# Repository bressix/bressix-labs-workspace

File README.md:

# bressix-labs-workspace

> Engineering Research & Development Laboratory
>
> Laboratório de Pesquisa e Desenvolvimento em Engenharia

---

*As versões em PT-BR estão disponíveis nos blocos expansíveis de cada seção.*

## Proof of Concept / Em Desenvolvimento

This repository is the main engineering workspace for **bressix LABs**.

Here you'll find projects at different stages of development. Some are production-ready and actively maintained, while others are early prototypes, experiments, or ongoing research. That diversity is intentional and reflects how we approach engineering.

We believe good engineering evolves through iteration. Ideas are tested, designs are refined, and documentation grows alongside the project. Rather than waiting for everything to be perfect, we prefer to share our work as it evolves.

Not every repository follows the same structure, contains the same level of documentation, or has the same degree of maturity. Each project is documented according to its own complexity and current stage of development.

The purpose of this workspace is to build, document, and share engineering projects as they evolve.

<details>
<summary><strong>PT-BR</strong></summary>

Este repositório é o principal ambiente de engenharia da **bressix LABs**.

Aqui você encontrará projetos em diferentes estágios de desenvolvimento. Alguns estão prontos para uso e são mantidos ativamente, enquanto outros ainda são protótipos, experimentos ou pesquisas em andamento. Essa diversidade é intencional e reflete a forma como fazemos engenharia.

Acreditamos que boa engenharia evolui por meio da iteração. Ideias são testadas, projetos são refinados e a documentação cresce junto com o próprio desenvolvimento. Em vez de esperar que tudo esteja perfeito, preferimos compartilhar nosso trabalho à medida que ele evolui.

Nem todos os repositórios seguem a mesma estrutura, possuem o mesmo nível de documentação ou apresentam o mesmo grau de maturidade. Cada projeto é documentado de acordo com sua complexidade e seu estágio de desenvolvimento.

O propósito deste workspace é construir, documentar e compartilhar projetos de engenharia à medida que evoluem.

</details>

## Disclaimer

#### NO WARRANTY

THIS WORKSPACE, INCLUDING ALL SOFTWARE, FIRMWARE, HARDWARE DESIGNS, SCHEMATICS, AND OTHER ASSETS, IS PROVIDED **"AS IS"**, WITHOUT WARRANTY OF ANY KIND, EXPRESS OR IMPLIED, INCLUDING, BUT NOT LIMITED TO, WARRANTIES OF MERCHANTABILITY, FITNESS FOR A PARTICULAR PURPOSE, NON-INFRINGEMENT, SECURITY, FUNCTIONALITY, RELIABILITY, OR HARDWARE SAFETY.

THE AUTHORS, CONTRIBUTORS, AND COPYRIGHT HOLDERS SHALL NOT BE LIABLE FOR ANY CLAIM, DAMAGES, LOSS OF DATA, DEVICE BRICKING, HARDWARE FAILURE, SECURITY INCIDENT, SERVICE INTERRUPTION, OR OTHER LIABILITY, WHETHER IN AN ACTION OF CONTRACT, TORT, OR OTHERWISE, ARISING FROM, OUT OF, OR IN CONNECTION WITH THIS WORKSPACE OR THE USE OF ANY SOFTWARE, FIRMWARE, HARDWARE DESIGN, SCHEMATIC, OR OTHER ASSET PROVIDED HEREIN.

USING, COMPILING, FLASHING, MODIFYING, OR DEPLOYING ANY CODE, FIRMWARE, HARDWARE DESIGN, OR OTHER ASSET FROM THIS REPOSITORY IS ENTIRELY AT YOUR OWN RISK.

THIS DISCLAIMER APPLIES TO THE ENTIRE WORKSPACE UNLESS A SPECIFIC PROJECT EXPLICITLY STATES OTHERWISE.

<details>
<summary><strong>PT-BR</strong></summary>

#### SEM GARANTIAS

ESTE WORKSPACE, INCLUINDO TODOS OS SOFTWARES, FIRMWARES, PROJETOS DE HARDWARE, ESQUEMÁTICOS E DEMAIS ATIVOS, É FORNECIDO **"NO ESTADO EM QUE SE ENCONTRA"**, SEM GARANTIAS DE QUALQUER NATUREZA, EXPRESSAS OU IMPLÍCITAS, INCLUINDO, MAS NÃO SE LIMITANDO A, GARANTIAS DE COMERCIALIZAÇÃO, ADEQUAÇÃO A UMA FINALIDADE ESPECÍFICA, NÃO VIOLAÇÃO, SEGURANÇA, FUNCIONALIDADE, CONFIABILIDADE OU INTEGRIDADE FÍSICA DO HARDWARE.

OS AUTORES, COLABORADORES E DETENTORES DOS DIREITOS AUTORAIS NÃO PODERÃO SER RESPONSABILIZADOS POR QUAISQUER RECLAMAÇÕES, DANOS, PERDA DE DADOS, INUTILIZAÇÃO DE DISPOSITIVOS (DEVICE BRICKING), FALHAS DE HARDWARE, INCIDENTES DE SEGURANÇA, INTERRUPÇÕES DE SERVIÇO OU OUTRAS RESPONSABILIDADES DECORRENTES DO USO DESTE WORKSPACE OU DE QUALQUER SOFTWARE, FIRMWARE, PROJETO DE HARDWARE, ESQUEMÁTICO OU OUTRO ATIVO DISPONIBILIZADO NESTE REPOSITÓRIO.

O USO, A COMPILAÇÃO, A GRAVAÇÃO (FLASHING), A MODIFICAÇÃO OU A IMPLANTAÇÃO DE QUALQUER CÓDIGO, FIRMWARE, PROJETO DE HARDWARE OU OUTRO ATIVO DESTE REPOSITÓRIO É DE INTEIRA RESPONSABILIDADE DO USUÁRIO.

ESTA ISENÇÃO DE RESPONSABILIDADE APLICA-SE A TODO O WORKSPACE, EXCETO QUANDO UM PROJETO ESPECÍFICO DECLARAR EXPRESSAMENTE O CONTRÁRIO.

</details>

## Security Notice

No private keys, cryptographic seeds, production certificates, active service tokens, customer credentials, or confidential corporate information are stored or tracked within this repository.

Development workflows follow repository sanitization practices, strict `.gitignore` policies, and isolated local environments to prevent accidental disclosure of sensitive information.

Local engineering activities should rely on detached configuration files, environment variables, or `.env` templates that are never committed to version control.

Repositories may intentionally include placeholder files, sample certificates, mock credentials, or template configurations for demonstration purposes. Such artifacts are non-functional and intended solely for development, testing, or documentation.

<details>
<summary><strong>PT-BR</strong></summary>

Nenhuma chave privada, semente criptográfica, certificado de produção, token ativo de serviço, credencial de cliente ou informação corporativa confidencial é armazenada ou rastreada neste repositório.

Os fluxos de desenvolvimento seguem práticas de higienização do repositório, políticas rigorosas de `.gitignore` e ambientes locais isolados para reduzir o risco de exposição acidental de informações sensíveis.

As atividades locais de engenharia devem utilizar arquivos de configuração desacoplados, variáveis de ambiente ou templates `.env` que nunca sejam enviados ao controle de versão.

Os repositórios podem conter arquivos de exemplo, certificados fictícios, credenciais simuladas ou configurações modelo destinados exclusivamente à demonstração, desenvolvimento, testes ou documentação. Esses artefatos não são funcionais e não representam credenciais reais.

</details>

## Mission Statement

bressix LABs exists to advance engineering through practical research, experimentation, and open documentation.

Our work spans multiple disciplines—including hardware, embedded systems, Linux, information security, PKI, automation, infrastructure, and applied research—but the mission remains the same: building practical solutions, documenting technical decisions, and sharing knowledge that others can study, reproduce, and extend.

We believe engineering knowledge becomes more valuable when it is documented, reproducible, and shared.

<details>
<summary><strong>PT-BR</strong></summary>

A bressix LABs existe para promover a engenharia por meio de pesquisa prática, experimentação e documentação aberta.

Nosso trabalho abrange diversas áreas — incluindo hardware, sistemas embarcados, Linux, segurança da informação, PKI, automação, infraestrutura e pesquisa aplicada — mas a missão permanece a mesma: desenvolver soluções práticas, documentar decisões técnicas e compartilhar conhecimento para que outras pessoas possam estudá-lo, reproduzi-lo e expandi-lo.

Acreditamos que o conhecimento de engenharia se torna mais valioso quando é documentado, reproduzível e compartilhado.

</details>

## Engineering Values

The projects in this workspace are diverse, but they are usually guided by the same engineering values.

- Simplicity is preferred over unnecessary complexity.
- Technical decisions are documented, not just their outcomes.
- Projects are shared as they evolve.
- Engineering history is preserved whenever it provides context or future value.
- Structure exists to support engineering, never the other way around.
- Practical solutions come before elegant abstractions.

These values are descriptive rather than prescriptive. They reflect the experience accumulated across different projects, not a checklist applied to every repository.

<details>
<summary><strong>PT-BR</strong></summary>

Os projetos deste workspace são bastante diferentes entre si, mas normalmente são guiados pelos mesmos valores de engenharia.

- Preferimos simplicidade à complexidade desnecessária.
- Documentamos decisões técnicas, não apenas seus resultados.
- Compartilhamos projetos à medida que evoluem.
- Preservamos o histórico de engenharia sempre que ele agrega contexto ou valor futuro.
- A estrutura existe para servir à engenharia, nunca o contrário.
- Soluções práticas vêm antes de abstrações elegantes.

Esses valores são descritivos, não prescritivos. Eles refletem a experiência acumulada em diferentes projetos, e não um checklist aplicado a todos os repositórios.

</details>

## Engineering Philosophy

We believe engineering is an iterative process.

Projects rarely begin as complete platforms. Most start as small experiments, evolve through practical use, and mature one decision at a time.

We strive to keep repositories as simple as possible, documentation proportional to each project's complexity, and engineering decisions easy to understand.

Nothing in this workspace exists simply because "every project should have one." Every component, document, script, and directory should exist because it serves a practical purpose.

<details>
<summary><strong>PT-BR</strong></summary>

Acreditamos que engenharia é um processo iterativo.

Projetos raramente nascem como plataformas completas. A maioria começa como pequenos experimentos, evolui por meio do uso prático e amadurece uma decisão de cada vez.

Buscamos manter os repositórios tão simples quanto possível, a documentação proporcional à complexidade de cada projeto e as decisões de engenharia fáceis de compreender.

Nada neste workspace existe apenas porque "todo projeto deveria ter". Cada componente, documento, script e diretório deve existir porque possui um propósito prático.

</details>

## Workspace Architecture

The workspace is organized by engineering domain rather than by technology or programming language. Each directory groups projects with similar objectives, allowing both the projects and the workspace to evolve naturally as new ideas, technologies, and research emerge.

```text
bressix-labs-workspace/
├── 3D/                        # Functional 3D modeling and mechanical CAD assets.
├── audio/                     # Audio engineering, DSP experiments, and acoustic studies.
├── firmware/                  # Embedded firmware development (ESP32, CH552, AVR, RP2350).
├── hardware/                  # Schematics, PCB layouts, hardware analysis, and pin mapping.
├── system-hacking-n-tuning/   # Linux customization, system tuning, drivers, and platform optimization.
├── tls-n-automation-scripts/  # PKI tooling, infrastructure utilities, automation scripts, and API integrations.
│   ├── cnpj_query/            # Resilient multi-provider CNPJ acquisition engine.
│   ├── globalsign-atlas-api/  # Atlas API integration modules.
│   ├── globalsign-gcc-api/    # Legacy GCC API integration modules.
│   ├── ssl-tls-auditing/      # TLS auditing and compliance validation tools.
│   ├── tls-crt/               # X.509 certificate manipulation utilities.
│   ├── tls-discovery/         # TLS asset discovery and inventory automation.
│   └── tls-scripts/           # Core cryptographic and infrastructure helper scripts.
└── WIP/                       # Experimental and unclassified development sandbox.
```

The structure is intentionally simple and may evolve as projects mature or new engineering domains are introduced.

<details>
<summary><strong>PT-BR</strong></summary>

O workspace é organizado por domínio de engenharia, e não por tecnologia ou linguagem de programação. Cada diretório reúne projetos com objetivos semelhantes, permitindo que tanto os projetos quanto o próprio workspace evoluam naturalmente à medida que novas ideias, tecnologias e pesquisas surgem.

A estrutura é intencionalmente simples e pode evoluir conforme os projetos amadurecem ou novos domínios de engenharia sejam incorporados.

</details>

## License

This workspace is licensed under the **GNU General Public License v3.0 (GPL-3.0)**.

Unless explicitly stated otherwise within an individual project, all source code, documentation, hardware designs, schematics, and other assets are distributed under the terms of the GPL-3.0.

See the [`LICENSE`](LICENSE) file for the complete license text.

<details>
<summary><strong>PT-BR</strong></summary>

Este workspace está licenciado sob a **GNU General Public License v3.0 (GPL-3.0)**.

Salvo indicação explícita em contrário dentro de um projeto específico, todo o código-fonte, documentação, projetos de hardware, esquemáticos e demais ativos são distribuídos sob os termos da GPL-3.0.

Consulte o arquivo [`LICENSE`](LICENSE) para o texto completo da licença.

</details>

---

Copyright (C) 2026 **bressix LABs**

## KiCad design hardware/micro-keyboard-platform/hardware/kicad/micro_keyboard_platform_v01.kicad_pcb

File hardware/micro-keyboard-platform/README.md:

# Micro Keyboard Platform (MKP)

> Modular physical keyboard platform for embedded systems.

---

## Overview

The **Micro Keyboard Platform (MKP)** is a compact and modular physical
keyboard platform designed for embedded systems.

MKP is not simply a keyboard matrix.

It is an active input device with its own microcontroller, responsible for
scanning the keyboard, processing key events, implementing layers and
communicating with the host system.

The central design principle is:

> **The MKP is a keyboard, not a keyboard matrix.**

The host does not need to know how the keyboard matrix works. It only needs
to consume the events generated by the MKP.

The current hardware revision is based on the **RP2040-Zero** and provides:

- 50 physical keys;
- 5 × 10 keyboard matrix;
- per-key diodes;
- native USB HID capability;
- UART host interface;
- I2C host interface;
- SPI host interface;
- programmable WS2812B RGB status indicator;
- dedicated external 5 V power input.

<details>
<summary><strong>PT-BR</strong></summary>

A **Micro Keyboard Platform (MKP)** é uma plataforma compacta e modular de
teclado físico desenvolvida para sistemas embarcados.

O MKP não é simplesmente uma matriz de teclas.

Ele é um dispositivo de entrada ativo, com seu próprio microcontrolador,
responsável pela varredura do teclado, processamento dos eventos,
implementação de layers e comunicação com o sistema hospedeiro.

O princípio central do projeto é:

> **O MKP é um teclado, não uma matriz de teclas.**

O host não precisa conhecer o funcionamento interno da matriz. Ele apenas
consome os eventos produzidos pelo MKP.

A revisão atual utiliza o **RP2040-Zero** e oferece:

- 50 teclas físicas;
- matriz 5 × 10;
- diodo individual por tecla;
- USB HID nativo;
- interface UART;
- interface I2C;
- interface SPI;
- indicador RGB programável WS2812B;
- entrada dedicada de alimentação externa de 5 V.

</details>

---

## Why MKP?

MKP originally started as a compact keyboard for a specific embedded
terminal.

During development, the project evolved beyond that original requirement.

Instead of creating a keyboard tied to one device, the architecture was
redesigned as an independent platform capable of being reused by different
hosts.

This allows the same keyboard hardware to be integrated into:

- microcontroller projects;
- Linux SBCs;
- portable terminals;
- cyberdecks;
- communication devices;
- instrumentation;
- experimental embedded systems;
- conventional computers through USB HID.

The hardware provides capabilities.

The firmware defines behavior.

<details>
<summary><strong>PT-BR</strong></summary>

O MKP nasceu originalmente como um teclado compacto para um terminal
embarcado específico.

Durante o desenvolvimento, o projeto evoluiu além dessa necessidade inicial.

Em vez de criar um teclado dependente de um único equipamento, a arquitetura
foi transformada em uma plataforma independente capaz de ser reutilizada por
diferentes hosts.

Isso permite utilizar o mesmo hardware em:

- projetos com microcontroladores;
- SBCs Linux;
- terminais portáteis;
- cyberdecks;
- equipamentos de comunicação;
- instrumentação;
- sistemas embarcados experimentais;
- computadores convencionais através de USB HID.

O hardware oferece capacidades.

O firmware define o comportamento.

</details>

---

## Architecture

~~~text
                         USB-C
                           │
                    ┌──────▼──────┐
                    │ RP2040-Zero │
                    │             │
                    │ Scan        │
                    │ Debounce    │
                    │ Keymap      │
                    │ Layers      │
                    │ Protocol    │
                    └──────┬──────┘
                           │
             ┌─────────────┼─────────────┐
             │             │             │
             ▼             ▼             ▼
        Matrix 5×10     Host I/O      WS2812B
          50 keys      UART/I2C/SPI     GP29
             │
             ▼
        Key events
~~~

The keyboard matrix belongs entirely to the MKP.

Matrix GPIOs are never exposed to the host.

---

## Keyboard

The Revision B keyboard uses a **5 × 10 electrical matrix** with
**50 physical switches**.

~~~text
┌────┬────┬────┬────┬────┬────┬────┬────┬────┬────┐
│ 1  │ 2  │ 3  │ 4  │ 5  │ 6  │ 7  │ 8  │ 9  │ 0  │
├────┼────┼────┼────┼────┼────┼────┼────┼────┼────┤
│ Q  │ W  │ E  │ R  │ T  │ Y  │ U  │ I  │ O  │ P  │
├────┼────┼────┼────┼────┼────┼────┼────┼────┼────┤
│ A  │ S  │ D  │ F  │ G  │ H  │ J  │ K  │ L  │ENT │
├────┼────┼────┼────┼────┼────┼────┼────┼────┼────┤
│ FN │CAPS│ Z  │ X  │ C  │ V  │ B  │ N  │ M  │CTRL│
└────┴────┴────┴────┴────┴────┴────┴────┴────┴────┘
~~~

The remaining switches provide:

~~~text
A / B / X / Y

UP / DOWN / LEFT / RIGHT

SPACE

SW49 — firmware-defined function
~~~

The exact function of special keys remains configurable by firmware.

---

## Hardware

| Component | Revision B |
|---|---|
| Controller | RP2040-Zero |
| Keyboard matrix | 5 × 10 |
| Physical switches | 50 |
| Switch type | 4.5 × 4.5 × 5.0 mm tactile |
| Matrix diodes | 1N4148W |
| Diode package | SOD-123 |
| RGB indicator | WS2812B-5050 |
| USB | Native RP2040 USB |
| Host connector | 4 signals + GND |
| Host protocols | UART / I2C / SPI |
| External power | 5 V |
| PCB | 2-layer FR-4 |
| PCB thickness | 1.6 mm |

---

## Host Interfaces

The MKP can communicate with a host through two fundamentally different
interfaces.

### USB

The native USB interface of the RP2040 allows the MKP to operate directly
as a USB HID keyboard.

### Embedded Host Interface

A dedicated connector exposes four configurable signals:

~~~text
HOST_SIG1
HOST_SIG2
HOST_SIG3
HOST_SIG4
GND
~~~

These signals support:

~~~text
UART
I2C
SPI
~~~

Protocol selection is handled entirely by firmware.

Revision B does **not** use hardware protocol-selection jumpers, ADC
identification or resistor networks.

---

## RGB Status Indicator

Revision B includes one **WS2812B-5050** addressable RGB LED connected to
GP29.

Its behavior is firmware-defined and may represent:

- initialization;
- active layer;
- communication mode;
- Caps Lock;
- activity;
- error conditions;
- application-specific status.

---

## Mechanical Philosophy

MKP follows a **mechanical-first** design approach.

Keyboard geometry is primarily determined by:

- ergonomics;
- key spacing;
- physical dimensions;
- enclosure constraints;
- future faceplate integration.

Electrical routing adapts to the keyboard geometry rather than defining it.

Revision B places:

~~~text
TOP
├── switches
└── WS2812B

BOTTOM
├── RP2040-Zero
├── matrix diodes
├── passive components
├── host connector
└── power connector
~~~

The earlier experimental dual-side footprints were intentionally removed
from Revision B.

---

## Repository Structure

~~~text
micro-keyboard-platform/
├── docs/
│   ├── mkp_electrical_specification.txt
│   ├── mkp_electrical_specification_legacy_2026-07-13.txt
│   ├── mkp_manifesto.txt
│   ├── mkp_manifesto_legacy_2026-07-13.txt
│   └── inspiracao.jpeg
│
├── firmware/
│   └── src/
│
├── hardware/
│   ├── datasheets/
│   ├── kicad/
│   │   ├── footprints/
│   │   ├── micro_keyboard_platform_v01.kicad_pcb
│   │   ├── micro_keyboard_platform_v01.kicad_pro
│   │   ├── micro_keyboard_platform_v01.kicad_sch
│   │   └── micro_keyboard_platform_v01.net
│   │
│   └── production/
│       ├── bom/
│       └── gerbers/
│
├── mechanical/
│   ├── enclosure/
│   └── faceplate/
│
├── .gitignore
└── README.md
~~~

---

## Documentation

The project documentation is intentionally separated by purpose.

### Current documentation

- [Project Manifesto](docs/mkp_manifesto.txt)  
  Design philosophy, project identity and architectural principles.

- [Electrical Specification](docs/mkp_electrical_specification.txt)  
  Electrical architecture, GPIO mapping, interfaces, matrix behavior and
  Revision B implementation details.

### Historical documentation

Previous project documents are preserved instead of being overwritten:

- [Legacy Manifesto — 2026-07-13](docs/mkp_manifesto_legacy_2026-07-13.txt)
- [Legacy Electrical Specification — 2026-07-13](docs/mkp_electrical_specification_legacy_2026-07-13.txt)

Engineering history is intentionally preserved when it helps explain how
the project evolved.

---

## Revision B Status

**Current stage: prototype development**

### Completed

- [x] Platform architecture
- [x] 5 × 10 matrix
- [x] 50-key layout
- [x] RP2040-Zero controller
- [x] GPIO mapping
- [x] Electrical schematic
- [x] Host interface
- [x] External power input
- [x] WS2812B status indicator
- [x] TOP/BOTTOM component organization
- [x] Preliminary component placement
- [x] Main component selection
- [x] Electrical architecture freeze

### In progress

- [ ] Receive production components
- [ ] Physically validate footprints
- [ ] Freeze final placement
- [ ] Route PCB
- [ ] Run final DRC
- [ ] Generate Gerbers
- [ ] Manufacture prototype
- [ ] Assemble prototype
- [ ] Electrical bring-up
- [ ] Keyboard matrix validation
- [ ] USB HID validation
- [ ] UART validation
- [ ] I2C validation
- [ ] SPI validation
- [ ] Firmware implementation

---

## Development Flow

~~~text
Components
    │
    ▼
Footprint validation
    │
    ▼
Final placement
    │
    ▼
PCB routing
    │
    ▼
DRC
    │
    ▼
Gerbers
    │
    ▼
Prototype
    │
    ▼
Bring-up
    │
    ▼
Firmware
    │
    ▼
Validation
~~~

MKP is developed incrementally.

Design decisions that depend on physical tolerances or real components are
validated against actual hardware before being considered final.

---

## Design Principles

The Revision B architecture reflects a few core engineering principles:

- The MKP is a keyboard, not a keyboard matrix.
- The host consumes events instead of controlling the matrix.
- Hardware provides capabilities; firmware defines behavior.
- Mechanical requirements come before routing convenience.
- Useful flexibility should be preserved.
- Complexity without practical benefit should be removed.
- Engineering decisions and their history should be documented.
- The platform must remain independent from any single host.

---

## License

This project is part of **bressix LABs** and follows the license of the
parent workspace unless explicitly stated otherwise.

**GNU General Public License v3.0 — GPL-3.0**

See the workspace `LICENSE` file for the complete license text.

---

## bressix LABs

**Micro Keyboard Platform** is developed as part of **bressix LABs**.

> Engineering Research & Development Laboratory  
> Laboratório de Pesquisa e Desenvolvimento em Engenharia

The workspace covers hardware, embedded systems, Linux, information
security, PKI, automation, infrastructure and applied engineering research.

---

Copyright (C) 2026 **bressix LABs**

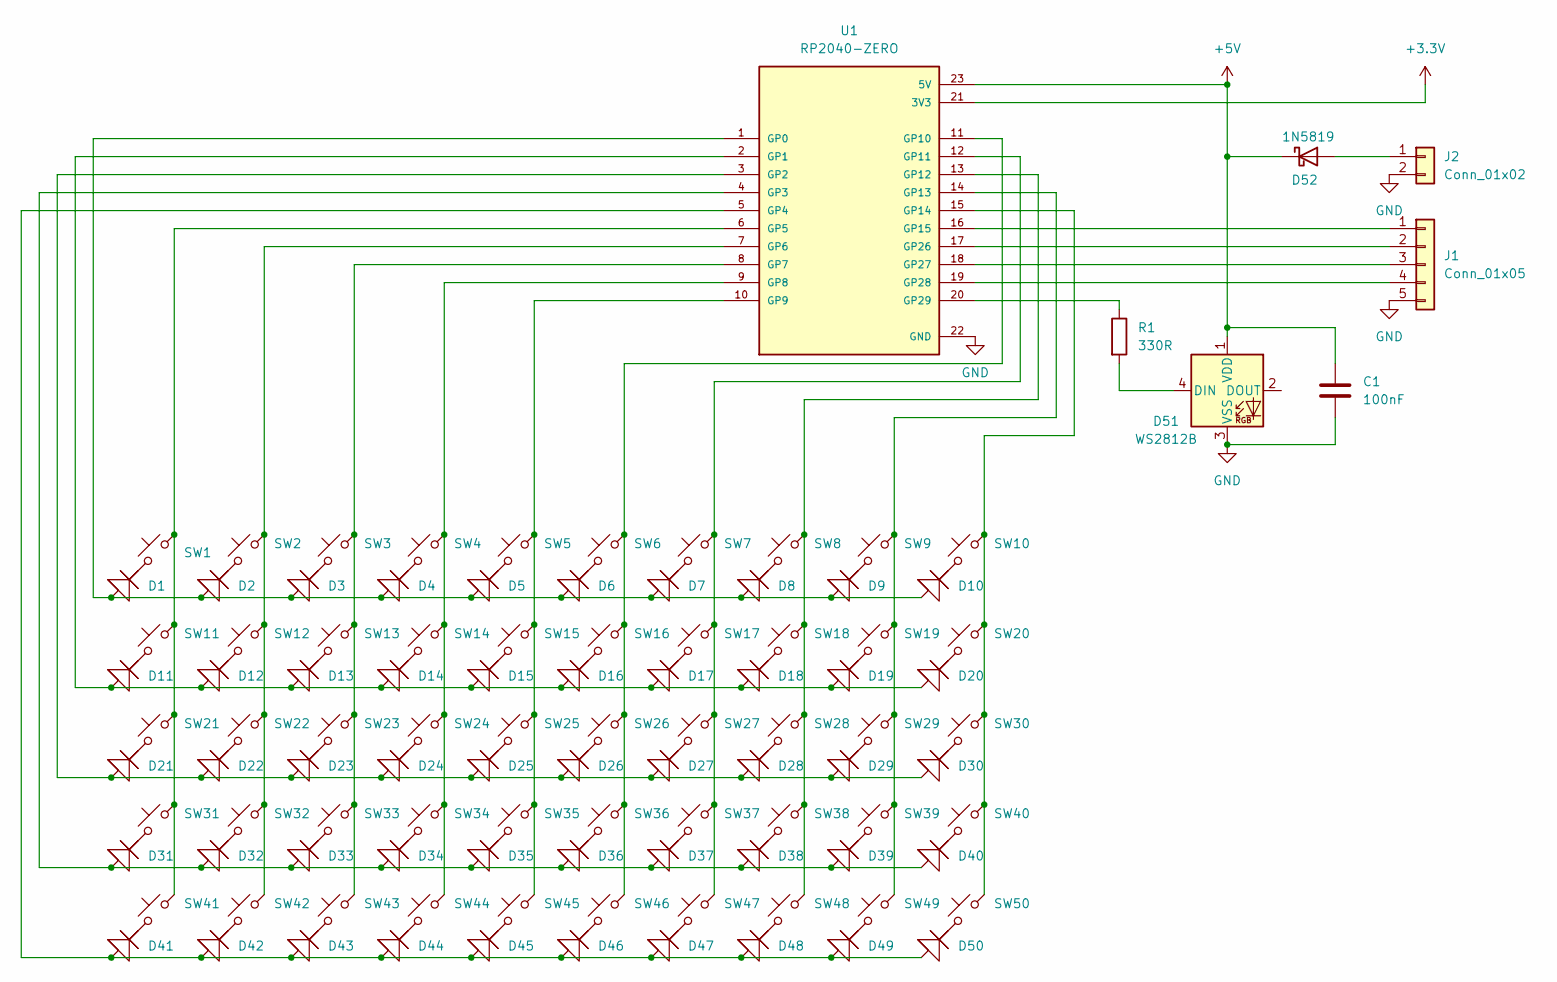
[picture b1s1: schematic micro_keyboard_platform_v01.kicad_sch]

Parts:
C1: 100nF; Capacitor_SMD_C_1206_3216Metric_BOTTON
D1, D2, D3, D4, D5, D6, D7, D8, D9, D10, D11, D12, D13, D14, D15, D16, D17, D18, D19, D20, D21, D22, D23, D24, D25, D26, D27, D28, D29, D30, D31, D32, D33, D34, D35, D36, D37, D38, D39, D40, D41, D42, D43, D44, D45, D46, D47, D48, D49, D50: 1N4148; D_SOD-123
D51: WS2812B; LED_WS2812B_PLCC4_5.0x5.0mm_P3.2mm
D52: 1N5819; Resistor_SMD_R_2010_5025Metric_BOTTON
J1: Conn_01x05; conn_01x05_hybrid_BOTTON
J2: Conn_01x02; JST_PH_S2B-PH-K_1x02_P2.00mm_Horizontal_BOTTON
R1: 330R; Resistor_SMD_R_2010_5025Metric_BOTTON
SW1, SW2, SW3, SW4, SW5, SW6, SW7, SW8, SW9, SW10, SW11, SW12, SW13, SW14, SW15, SW16, SW17, SW18, SW19, SW20, SW21, SW22, SW23, SW24, SW25, SW26, SW27, SW28, SW29, SW30, SW31, SW32, SW33, SW34, SW35, SW36, SW37, SW38, SW39, SW40, SW41, SW42, SW43, SW44, SW45, SW46, SW47, SW48, SW49, SW50: SW_Push_45deg; sw_push_4.5x4.5mm
U1: RP2040-ZERO; RP2040_ZERO_casteled_BOTTON; PARTREV NA

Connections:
+3.3V: U1.21 (3V3)
+5V: C1.1, D51.1 (VDD), D52.1 (K), U1.23 (5V)
GND: C1.2, D51.3 (VSS), J1.5, J2.2, U1.22 (GND)
unnamed: D1.1 (Anode), D2.1 (Anode), D3.1 (Anode), D4.1 (Anode), D5.1 (Anode), D6.1 (Anode), D7.1 (Anode), D8.1 (Anode), D9.1 (Anode), D10.1 (Anode), U1.1 (GP0)
unnamed: D1.2 (Cathode), SW1.1
unnamed: D2.2 (Cathode), SW2.1
unnamed: D3.2 (Cathode), SW3.1
unnamed: D4.2 (Cathode), SW4.1
unnamed: D5.2 (Cathode), SW5.1
unnamed: D6.2 (Cathode), SW6.1
unnamed: D7.2 (Cathode), SW7.1
unnamed: D8.2 (Cathode), SW8.1
unnamed: D9.2 (Cathode), SW9.1
unnamed: D10.2 (Cathode), SW10.1
unnamed: D11.1 (Anode), D12.1 (Anode), D13.1 (Anode), D14.1 (Anode), D15.1 (Anode), D16.1 (Anode), D17.1 (Anode), D18.1 (Anode), D19.1 (Anode), D20.1 (Anode), U1.2 (GP1)
unnamed: D11.2 (Cathode), SW11.1
unnamed: D12.2 (Cathode), SW12.1
unnamed: D13.2 (Cathode), SW13.1
unnamed: D14.2 (Cathode), SW14.1
unnamed: D15.2 (Cathode), SW15.1
unnamed: D16.2 (Cathode), SW16.1
unnamed: D17.2 (Cathode), SW17.1
unnamed: D18.2 (Cathode), SW18.1
unnamed: D19.2 (Cathode), SW19.1
unnamed: D20.2 (Cathode), SW20.1
unnamed: D21.1 (Anode), D22.1 (Anode), D23.1 (Anode), D24.1 (Anode), D25.1 (Anode), D26.1 (Anode), D27.1 (Anode), D28.1 (Anode), D29.1 (Anode), D30.1 (Anode), U1.3 (GP2)
unnamed: D21.2 (Cathode), SW21.1
unnamed: D22.2 (Cathode), SW22.1
unnamed: D23.2 (Cathode), SW23.1
unnamed: D24.2 (Cathode), SW24.1
unnamed: D25.2 (Cathode), SW25.1
unnamed: D26.2 (Cathode), SW26.1
unnamed: D27.2 (Cathode), SW27.1
unnamed: D28.2 (Cathode), SW28.1
unnamed: D29.2 (Cathode), SW29.1
unnamed: D30.2 (Cathode), SW30.1
unnamed: D31.1 (Anode), D32.1 (Anode), D33.1 (Anode), D34.1 (Anode), D35.1 (Anode), D36.1 (Anode), D37.1 (Anode), D38.1 (Anode), D39.1 (Anode), D40.1 (Anode), U1.4 (GP3)
unnamed: D31.2 (Cathode), SW31.1
unnamed: D32.2 (Cathode), SW32.1
unnamed: D33.2 (Cathode), SW33.1
unnamed: D34.2 (Cathode), SW34.1
unnamed: D35.2 (Cathode), SW35.1
unnamed: D36.2 (Cathode), SW36.1
unnamed: D37.2 (Cathode), SW37.1
unnamed: D38.2 (Cathode), SW38.1
unnamed: D39.2 (Cathode), SW39.1
unnamed: D40.2 (Cathode), SW40.1
unnamed: D41.1 (Anode), D42.1 (Anode), D43.1 (Anode), D44.1 (Anode), D45.1 (Anode), D46.1 (Anode), D47.1 (Anode), D48.1 (Anode), D49.1 (Anode), D50.1 (Anode), U1.5 (GP4)
unnamed: D41.2 (Cathode), SW41.1
unnamed: D42.2 (Cathode), SW42.1
unnamed: D43.2 (Cathode), SW43.1
unnamed: D44.2 (Cathode), SW44.1
unnamed: D45.2 (Cathode), SW45.1
unnamed: D46.2 (Cathode), SW46.1
unnamed: D47.2 (Cathode), SW47.1
unnamed: D48.2 (Cathode), SW48.1
unnamed: D49.2 (Cathode), SW49.1
unnamed: D50.2 (Cathode), SW50.1
unnamed: D51.4 (DIN), R1.2
unnamed: D52.2 (A), J2.1
unnamed: J1.1, U1.16 (GP15)
unnamed: J1.2, U1.17 (GP26)
unnamed: J1.3, U1.18 (GP27)
unnamed: J1.4, U1.19 (GP28)
unnamed: SW1.2, SW11.2, SW21.2, SW31.2, SW41.2, U1.6 (GP5)
unnamed: SW2.2, SW12.2, SW22.2, SW32.2, SW42.2, U1.7 (GP6)
unnamed: SW3.2, SW13.2, SW23.2, SW33.2, SW43.2, U1.8 (GP7)
unnamed: SW4.2, SW14.2, SW24.2, SW34.2, SW44.2, U1.9 (GP8)
unnamed: SW5.2, SW15.2, SW25.2, SW35.2, SW45.2, U1.10 (GP9)
unnamed: SW6.2, SW16.2, SW26.2, SW36.2, SW46.2, U1.11 (GP10)
unnamed: SW7.2, SW17.2, SW27.2, SW37.2, SW47.2, U1.12 (GP11)
unnamed: SW8.2, SW18.2, SW28.2, SW38.2, SW48.2, U1.13 (GP12)
unnamed: SW9.2, SW19.2, SW29.2, SW39.2, SW49.2, U1.14 (GP13)
unnamed: SW10.2, SW20.2, SW30.2, SW40.2, SW50.2, U1.15 (GP14)
unnamed: R1.1, U1.20 (GP29)

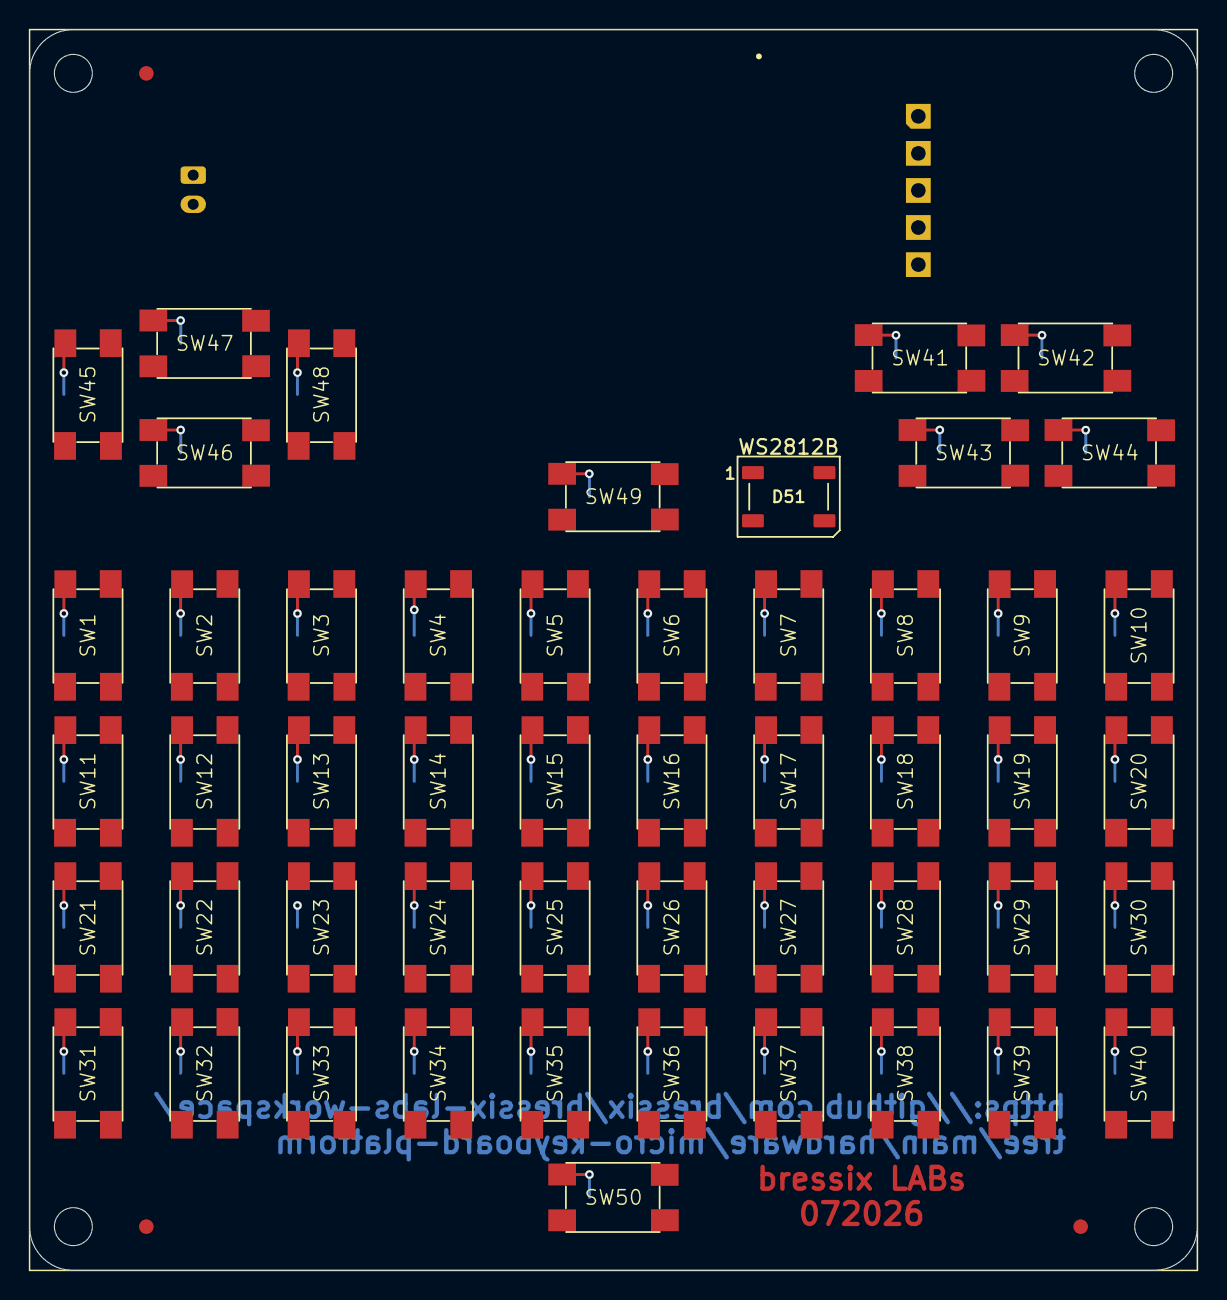
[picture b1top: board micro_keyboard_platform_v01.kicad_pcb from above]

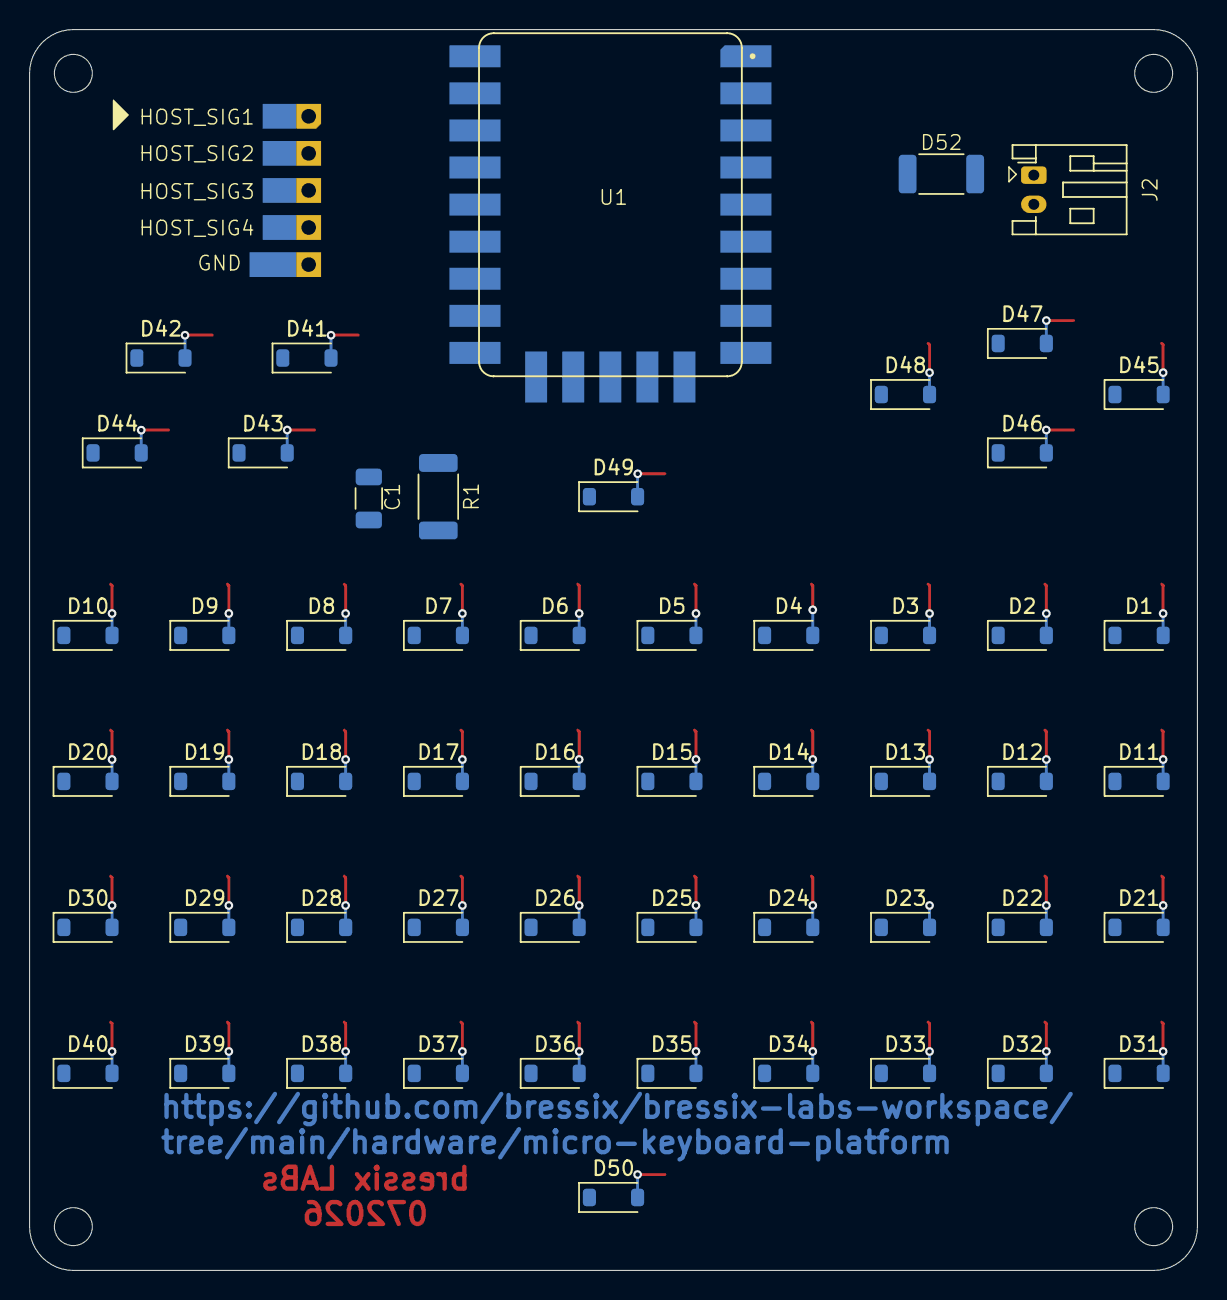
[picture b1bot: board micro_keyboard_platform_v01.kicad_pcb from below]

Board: 2 copper layers, 80.0 x 85.0 mm, 107 parts (50 on the bottom side), 74 nets.

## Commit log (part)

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2026-06-13 infra: initial repository layout and module tree definition
2026-06-13 infra: remove redundant .gitkeep from repository root
2026-06-13 feat(tls-n-automation): migrate validated cnpj_query script to its dedicated module
2026-06-18 docs(cnpj_query): deploy high-tier bilingual documentation and architecture flow
2026-06-18 chore(infra): deploy global gitignore security policies
2026-06-18 docs(infra): update master workspace readme with bressix labs standard
2026-06-18 docs(cnpj-query): deploy finalized structural layout and module roadmap
2026-06-18 chore(infra): sharpen global gitignore with API dumps, python metadata and lab output constraints
2026-06-29 chore(infra): isolate local untracked drafts

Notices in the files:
README.md:
License: GPLv3
